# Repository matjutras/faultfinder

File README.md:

# FaultFinder

See `CLAUDE.md` for architecture and conventions.

## Backend

```
cd backend
python3 -m venv .venv && .venv/bin/pip install -r requirements.txt
.venv/bin/uvicorn app.main:app --reload
.venv/bin/pytest -v
```

Requires `ngspice` on PATH (`sudo apt-get install ngspice`) and `kicad` for
`kicad-cli` (`sudo apt-get install kicad`).

`map.json` and `faults.json` under each `devices/*/` are generated, not
committed (see CLAUDE.md) — after a fresh checkout, regenerate them once per
device:

```
curl -X POST http://localhost:8000/api/devices/voltage_divider_01/import
```

## Frontend

```
cd frontend
npm install
npm run dev
npm test
```

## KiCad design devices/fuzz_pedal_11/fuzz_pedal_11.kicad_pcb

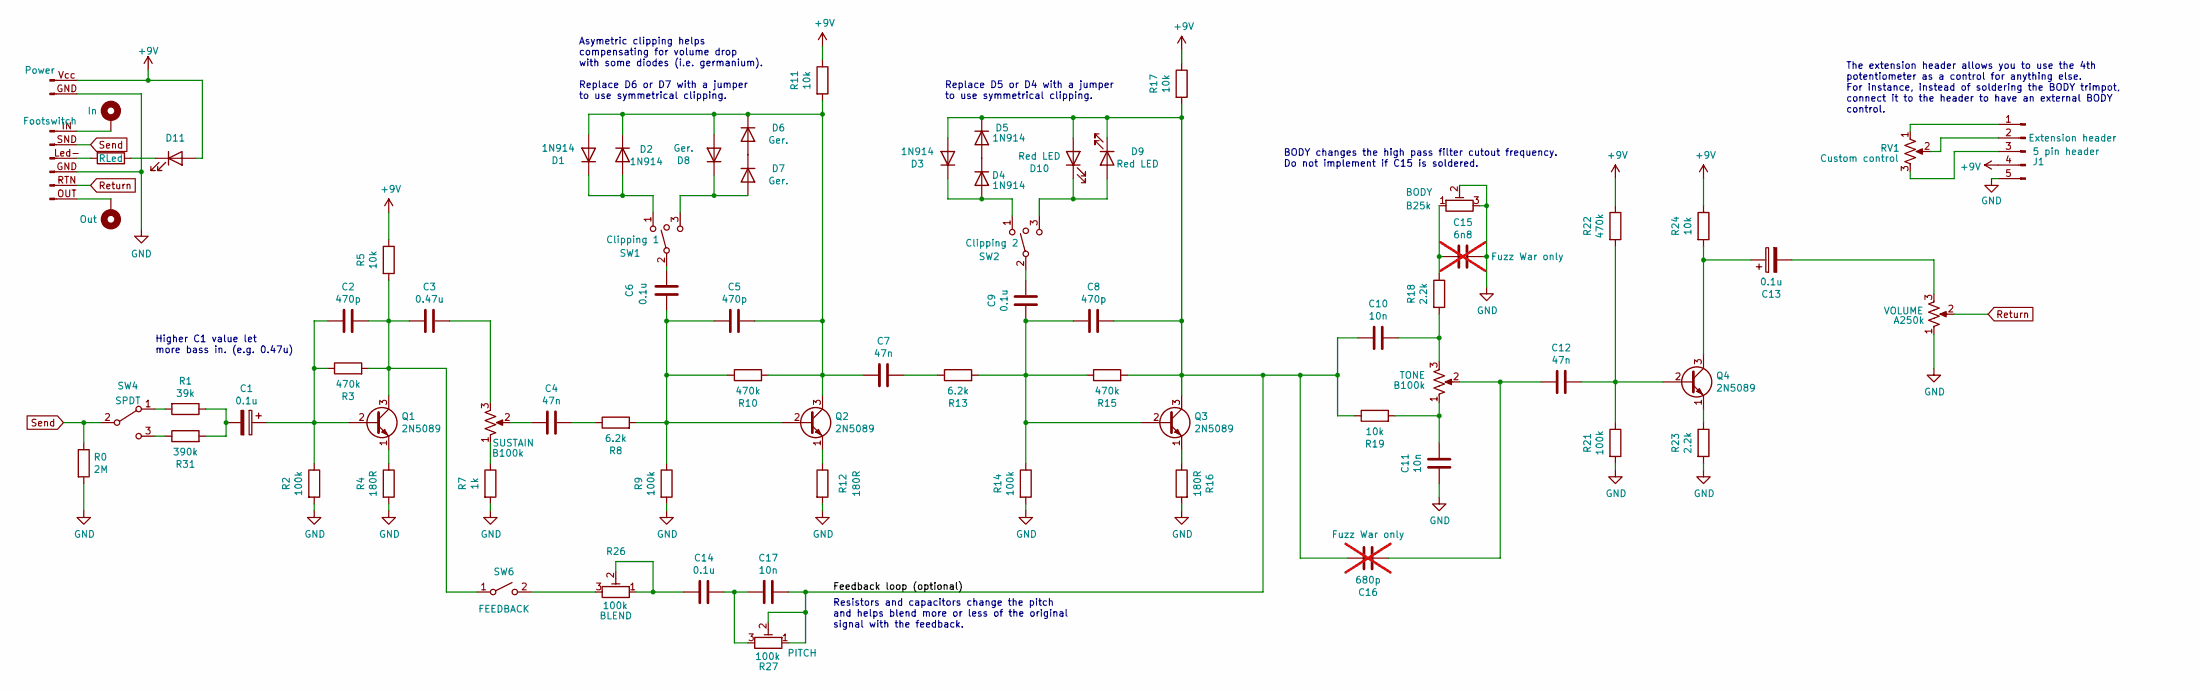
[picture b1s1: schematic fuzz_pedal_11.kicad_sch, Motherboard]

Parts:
C1, C6, C9, C14: 0.1u; C_Rect_L7.2mm_W2.5mm_P5.00mm_FKS2_FKP2_MKS2_MKP2
C2, C5, C8: 470p; C_Rect_L7.2mm_W4.5mm_P5.00mm_FKS2_FKP2_MKS2_MKP2
C3: 0.47u; C_Rect_L7.2mm_W2.5mm_P5.00mm_FKS2_FKP2_MKS2_MKP2
C4, C7, C12: 47n; C_Rect_L7.2mm_W2.5mm_P5.00mm_FKS2_FKP2_MKS2_MKP2
C10, C11, C17: 10n; C_Rect_L7.2mm_W2.5mm_P5.00mm_FKS2_FKP2_MKS2_MKP2
C13: 0.1u; C_Rect_L7.2mm_W3.0mm_P5.00mm_FKS2_FKP2_MKS2_MKP2
C15: 6n8; C_Rect_L7.2mm_W2.5mm_P5.00mm_FKS2_FKP2_MKS2_MKP2; not fitted
C16: 680p; C_Rect_L7.2mm_W2.5mm_P5.00mm_FKS2_FKP2_MKS2_MKP2; not fitted
D1, D2, D3, D4, D5: 1N914; D_DO-35_SOD27_P7.62mm_Horizontal
D6, D7, D8: Ger.; D_DO-35_SOD27_P7.62mm_Horizontal
D9, D10: Red LED; LED_D5.0mm
D11: LED 5mm; LED_D5.0mm
DC-Header1: JST connector 2 pin; Connector_Header_DC
H1: In; SolderWire-0.5sqmm_1x01_D0.9mm_OD2.1mm
H2: Out; SolderWire-0.5sqmm_1x01_D0.9mm_OD2.1mm
J1: 5 pin header; PinSocket_1x05_P2.54mm_Vertical
Q1, Q2, Q3, Q4: 2N5089; TO-92_Inline_Wide
R0: 2M; R_Axial_DIN0207_L6.3mm_D2.5mm_P7.62mm_Horizontal
R1: 39k; R_Axial_DIN0207_L6.3mm_D2.5mm_P7.62mm_Horizontal
R2, R9, R14, R21: 100k; R_Axial_DIN0207_L6.3mm_D2.5mm_P7.62mm_Horizontal
R3, R10, R15, R22: 470k; R_Axial_DIN0207_L6.3mm_D2.5mm_P7.62mm_Horizontal
R4, R12, R16: 180R; R_Axial_DIN0207_L6.3mm_D2.5mm_P7.62mm_Horizontal
R5, R11, R17, R19, R24: 10k; R_Axial_DIN0207_L6.3mm_D2.5mm_P7.62mm_Horizontal
R6, R20: B100k; Potentiometer_Alpha_16mm_angled
R7: 1k; R_Axial_DIN0207_L6.3mm_D2.5mm_P7.62mm_Horizontal
R8, R13: 6.2k; R_Axial_DIN0207_L6.3mm_D2.5mm_P7.62mm_Horizontal
R18, R23: 2.2k; R_Axial_DIN0207_L6.3mm_D2.5mm_P7.62mm_Horizontal
R25: A250k; Potentiometer_Alpha_16mm_angled
R26, R27: 100k; Potentiometer_Vishay_T73YP_Vertical
R29: 4k; R_Axial_DIN0207_L6.3mm_D2.5mm_P7.62mm_Horizontal
R30: B25k; Potentiometer_Vishay_T73YP_Vertical
R31: 390k; R_Axial_DIN0207_L6.3mm_D2.5mm_P7.62mm_Horizontal
RV1: ?; Potentiometer_Alpha_16mm_angled
SW1, SW2: SPDT on-off-on; SW_SPDT_Lugs
SW4: SPDT; SW_SPDT_Lugs
SW6: 2.54 pin header to Footswitch; SolderWire-0.5sqmm_1x02_P2.54mm_D0.9mm_OD2.1mm
Switch-Header1: JST connector 2 pin; Connector_Header_Switch

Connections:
+9V: D11.2 (A), DC-Header1.Vcc (Pin_1), J1.4, R5.1, R11.1, R17.1, R22.1, R24.1
/Feedback loop: C8.1, C10.2, C16.1, C17.1, D3.2 (A), D5.1 (K), D9.1 (K), D10.2 (A), Q3.3 (C), R15.2, R17.2, R19.1, R27.1, R27.2
GND: C11.2, C15.1, DC-Header1.GND (Pin_2), J1.5, R0.2, R2.2, R4.2, R7.2, R9.2, R12.2, R14.2, R16.2, R21.2, R23.2, R25.1, R30.2, R30.3, Switch-Header1.GND (Pin_5)
unnamed: C1.2, R1.1, R31.2
unnamed: C3.1, R6.3
unnamed: C4.1, R8.1
unnamed: C4.2, R6.2
unnamed: C6.2, SW1.2
unnamed: C7.1, R13.1
unnamed: C9.1, SW2.2
unnamed: C10.1, R18.2, R20.3
unnamed: C11.1, R19.2, R20.1
unnamed: C12.2, C16.2, R20.2
unnamed: C13.2, R25.3
unnamed: C14.1, C17.2, R27.3
unnamed: C14.2, R26.1, R26.2
unnamed: C15.2, R18.1, R30.1
unnamed: C5.1, C7.2, D1.2 (A), D2.1 (K), D6.1 (K), D8.2 (A), Q2.3 (C), R10.2, R11.2
unnamed: D1.1 (K), D2.2 (A), SW1.1
unnamed: D3.1 (K), D4.2 (A), SW2.1
unnamed: D4.1 (K), D5.2 (A)
unnamed: D6.2 (A), D7.1 (K)
unnamed: D7.2 (A), D8.1 (K), SW1.3
unnamed: D9.2 (A), D10.1 (K), SW2.3
unnamed: D11.1 (K), R29.1
unnamed: J1.1, RV1.1
unnamed: J1.2, RV1.2
unnamed: J1.3, RV1.3
unnamed: C1.1, C2.2, Q1.2 (B), R2.1, R3.1
unnamed: C2.1, C3.2, Q1.3 (C), R3.2, R5.2, SW6.1 (A)
unnamed: Q1.1 (E), R4.1
unnamed: C5.2, C6.1, Q2.2 (B), R8.2, R9.1, R10.1
unnamed: Q2.1 (E), R12.1
unnamed: C8.2, C9.2, Q3.2 (B), R13.2, R14.1, R15.1
unnamed: Q3.1 (E), R16.1
unnamed: C12.1, Q4.2 (B), R21.1, R22.2
unnamed: C13.1, Q4.3 (C), R24.2
unnamed: Q4.1 (E), R23.1
unnamed: R6.1, R7.1
unnamed: R1.2, SW4.1 (A)
unnamed: R31.1, SW4.3 (C)
unnamed: R26.3, SW6.2 (B)
unnamed: H1.1, Switch-Header1.IN (Pin_1)
unnamed: R29.2, Switch-Header1.Led- (Pin_4)
unnamed: H2.1, Switch-Header1.OUT (Pin_7)
Return: R25.2, Switch-Header1.RTN (Pin_6)
Send: R0.1, SW4.2 (B), Switch-Header1.SND (Pin_2)

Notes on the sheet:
BODY changes the high pass filter cutout frequency. Do not implement if C15 is soldered.
Resistors and capacitors change the pitch and helps blend more or less of the original signal with the feedback.
Higher C1 value let more bass in. (e.g. 0.47u)
The extension header allows you to use the 4th potentiometer as a control for anything else. For instance, instead of soldering the BODY trimpot, connect it to the header to have an external BODY control.
Replace D5 or D4 with a jumper to use symmetrical clipping.
Asymetric clipping helps compensating for volume drop with some diodes (i.e. germanium). Replace D6 or D7 with a jumper to use symmetrical clipping.

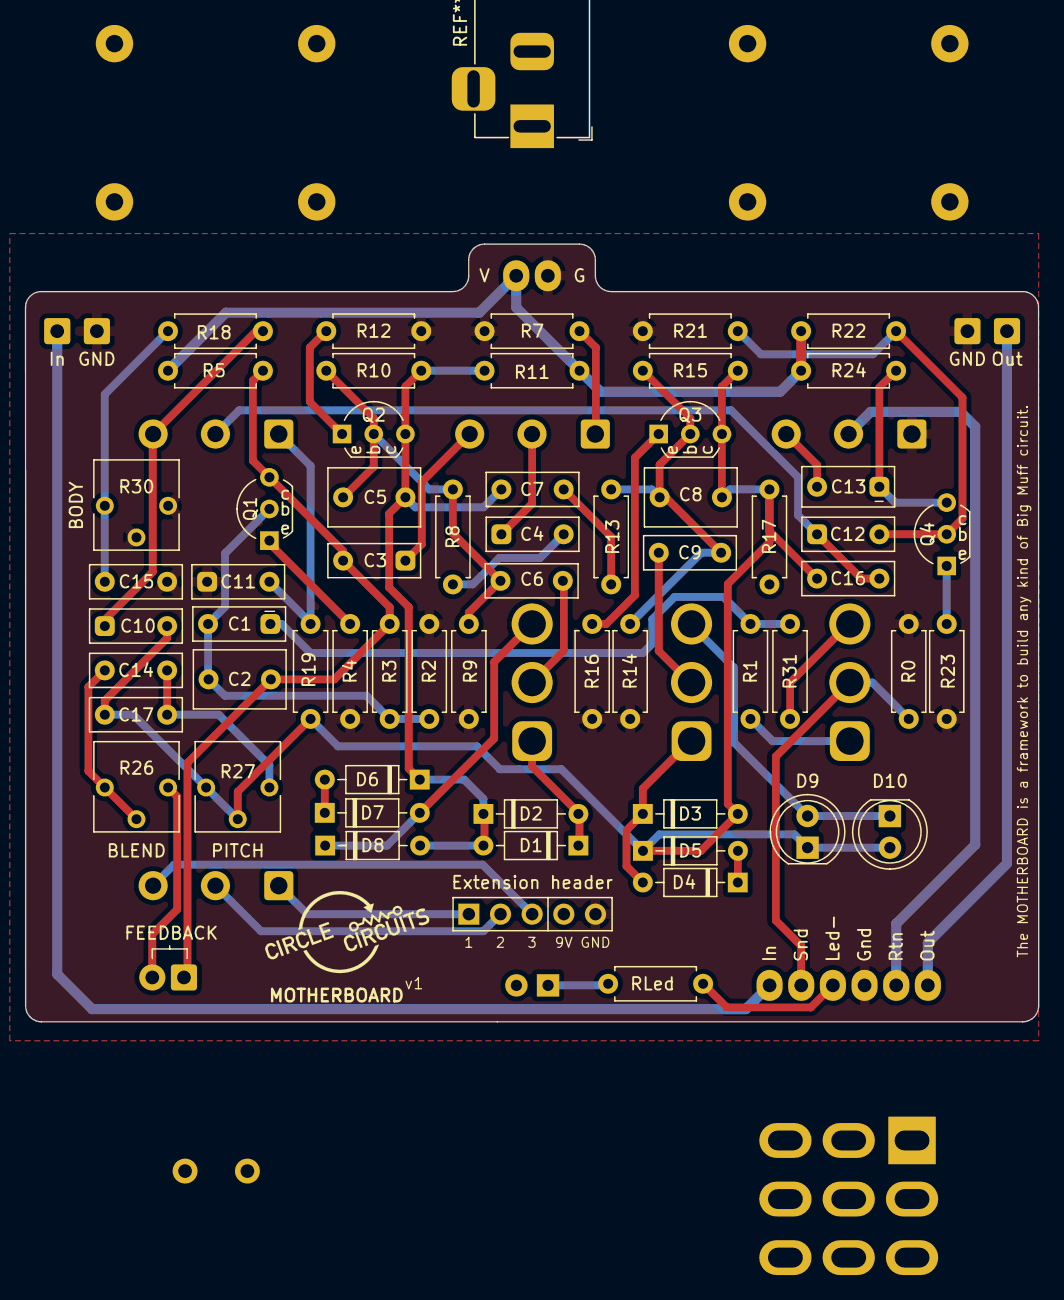
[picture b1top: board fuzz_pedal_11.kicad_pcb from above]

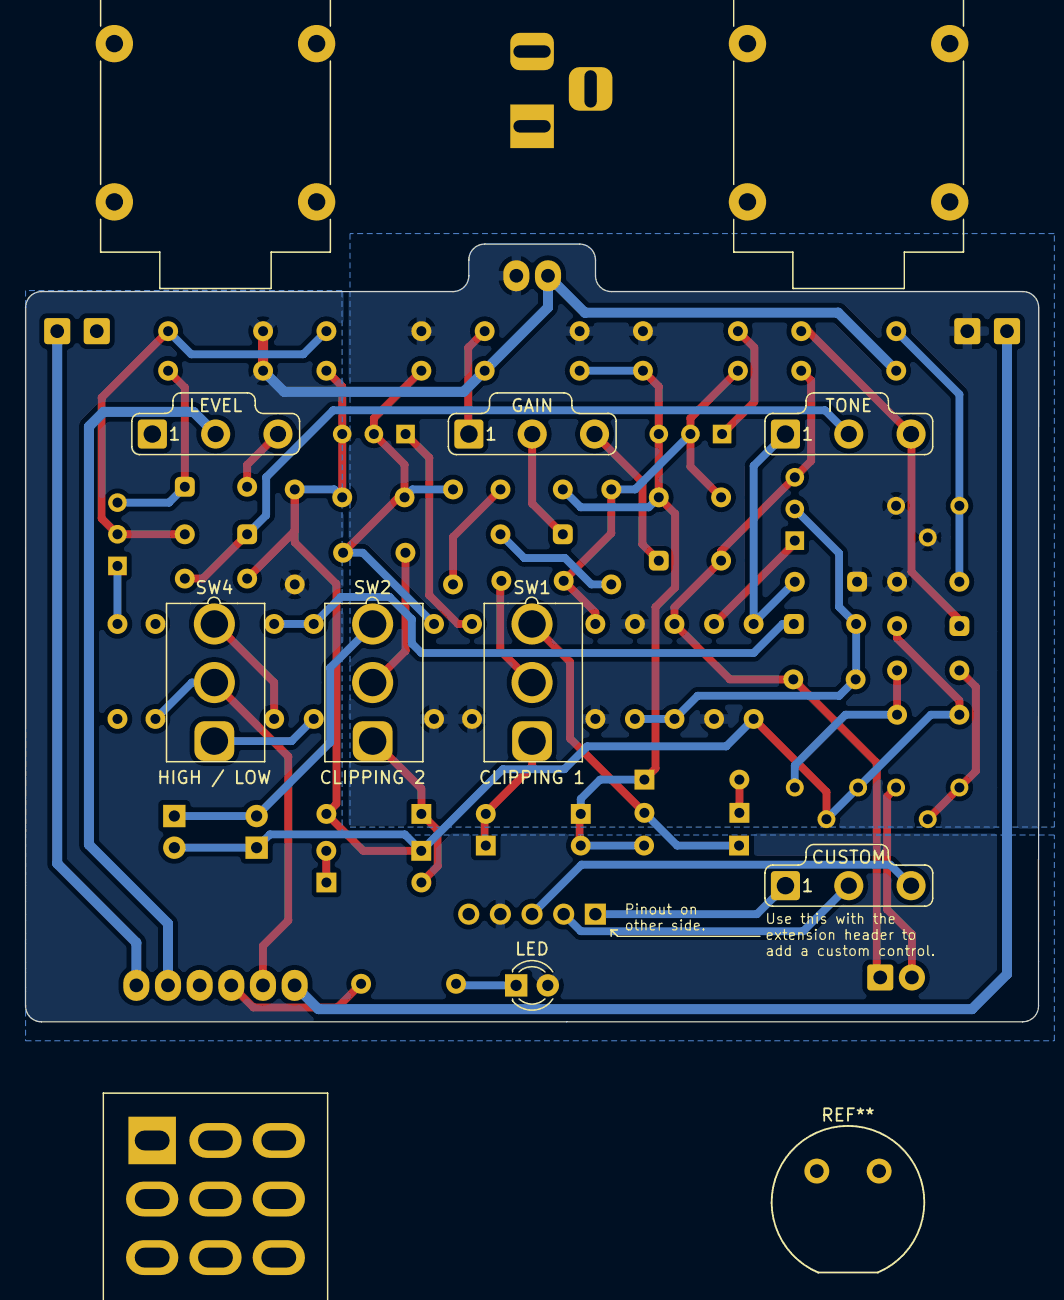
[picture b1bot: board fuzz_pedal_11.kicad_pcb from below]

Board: 2 copper layers, 81.3 x 62.4 mm, 74 parts (9 on the bottom side), 47 nets.

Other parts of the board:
Ref: Val; Switch_Alpha_SF17010F-0302-21R-L.step

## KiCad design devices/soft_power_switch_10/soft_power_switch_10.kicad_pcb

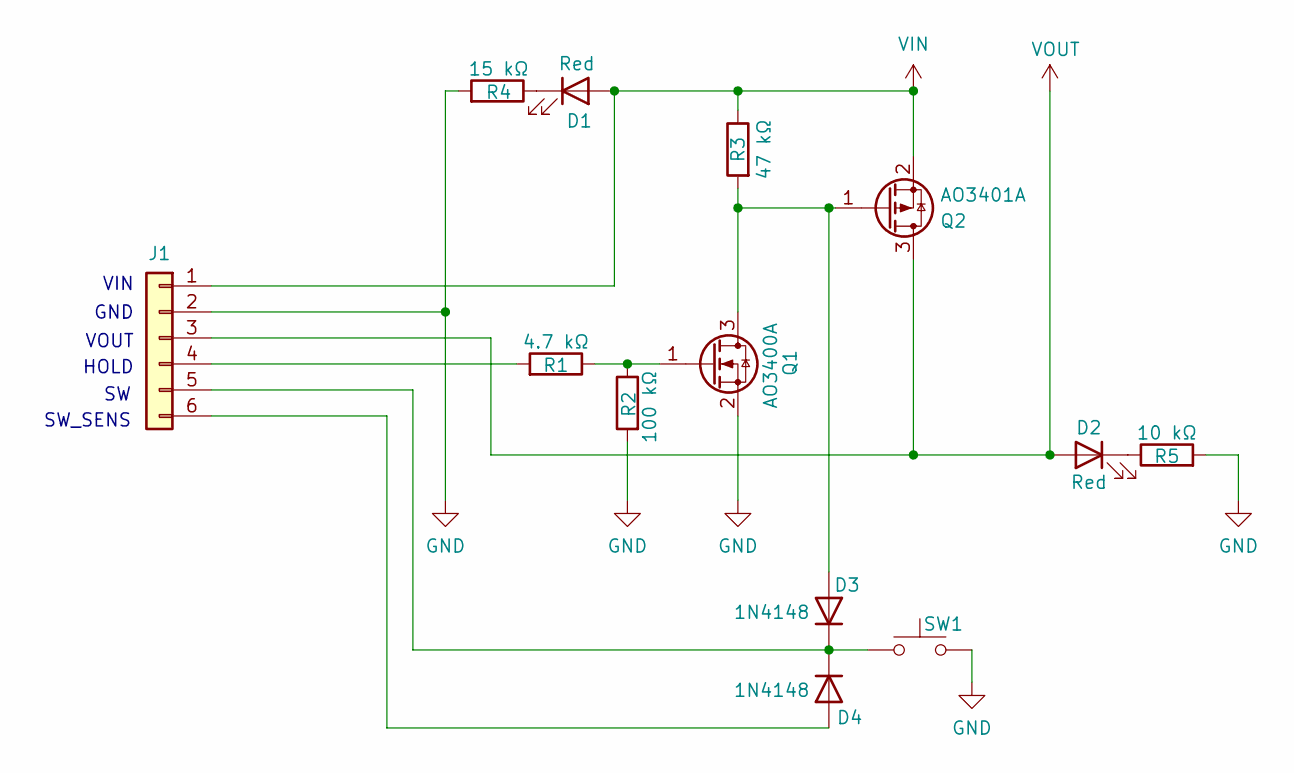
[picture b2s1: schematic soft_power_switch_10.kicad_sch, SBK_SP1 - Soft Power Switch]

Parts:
D1, D2: Red; LED_0603_1608Metric
D3, D4: 1N4148; D_SOD-323; LCSC C2128
J1: Conn_01x06; PinHeader_1x06_P2.54mm_Vertical
Q1: AO3400A; SOT-23
Q2: AO3401A; SOT-23
R1: 4.7 kΩ; R_0402_1005Metric
R2: 100 kΩ; R_0603_1608Metric
R3: 47 kΩ; R_0402_1005Metric
R4: 15 kΩ; R_0402_1005Metric
R5: 10 kΩ; R_0402_1005Metric
SW1: TS-1088-AR02016; SW_SPST_TS-1088-xR020; LCSC C720477

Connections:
GND: J1.2, Q1.2 (S), R2.2, R4.2, R5.2, SW1.2
unnamed: D1.1 (K), R4.1
unnamed: D2.1 (K), R5.1
unnamed: D3.2 (A), Q1.3 (D), Q2.1 (G), R3.2
unnamed: D3.1 (K), D4.1 (K), J1.5, SW1.1
unnamed: D4.2 (A), J1.6
unnamed: J1.4, R1.2
unnamed: Q1.1 (G), R1.1, R2.1
VIN: D1.2 (A), J1.1, Q2.2 (S), R3.1
VOUT: D2.2 (A), J1.3, Q2.3 (D)

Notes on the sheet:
VOUT
VIN
HOLD
SW_SENS
GND

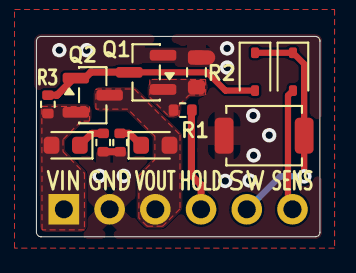
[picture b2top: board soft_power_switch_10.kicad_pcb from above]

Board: 2 copper layers, 15.7 x 11.1 mm, 13 parts (1 on the bottom side), 10 nets.

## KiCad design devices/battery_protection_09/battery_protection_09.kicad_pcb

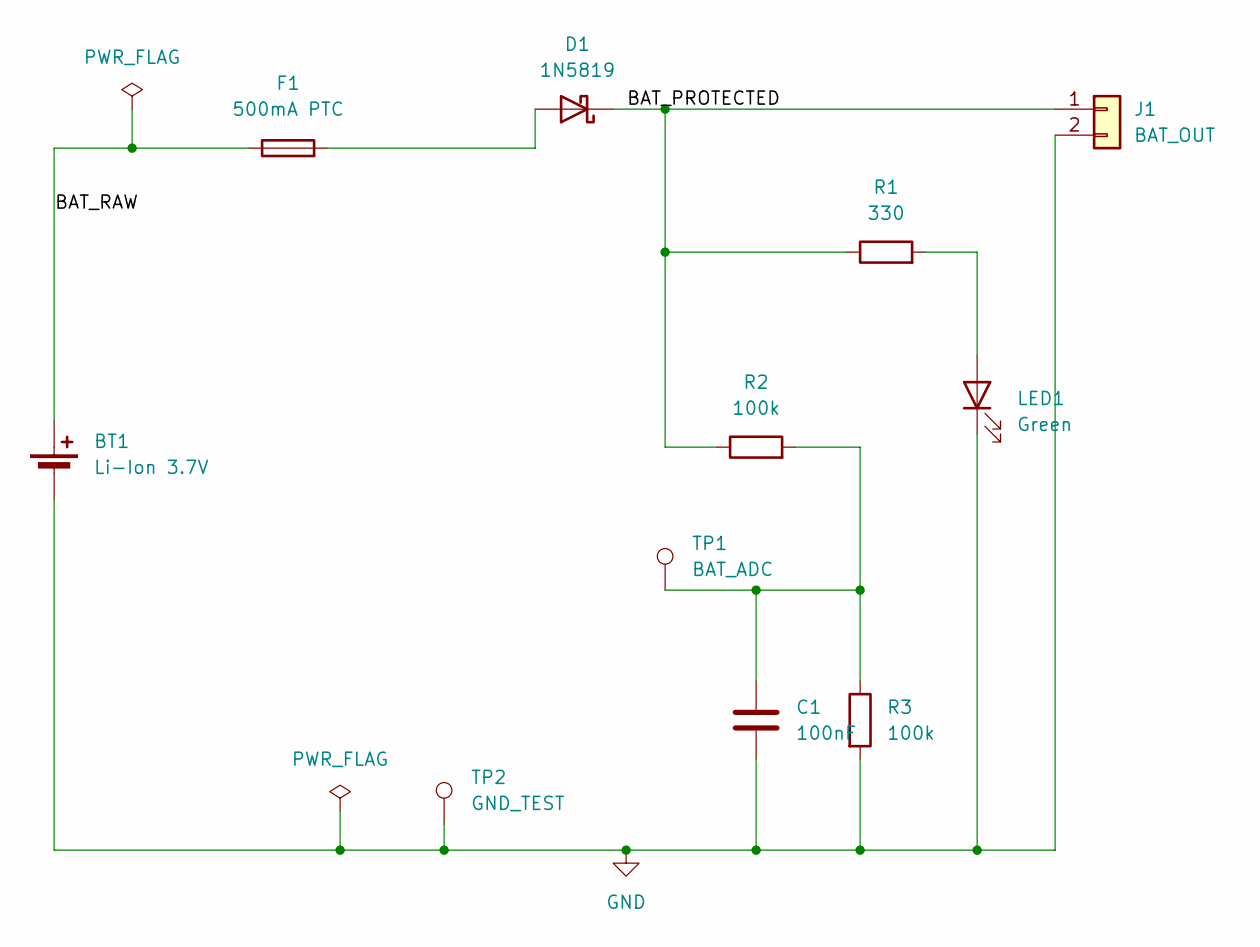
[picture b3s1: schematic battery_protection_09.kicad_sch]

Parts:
BT1: Li-Ion 3.7V; BatteryHolder_Keystone_1042_1x18650
C1: 100nF; C_0805_2012Metric
D1: 1N5819; D_SMA
F1: 500mA PTC; Fuse_1206_3216Metric
J1: BAT_OUT; PinHeader_1x02_P2.54mm_Vertical
LED1: Green; LED_0805_2012Metric
R1: 330; R_0805_2012Metric
R2, R3: 100k; R_0805_2012Metric
TP1: BAT_ADC; TestPoint_Pad_D1.5mm
TP2: GND_TEST; TestPoint_Pad_D1.5mm

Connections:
/BAT_PROTECTED: D1.1 (K), J1.1, R1.1, R2.1
/BAT_RAW: BT1.1 (+), F1.1
GND: BT1.2 (-), C1.2, J1.2, LED1.1 (K), R3.2, TP2.1 (1_1)
unnamed: C1.1, R2.2, R3.1, TP1.1 (1_1)
unnamed: D1.2 (A), F1.2
unnamed: LED1.2 (A), R1.2

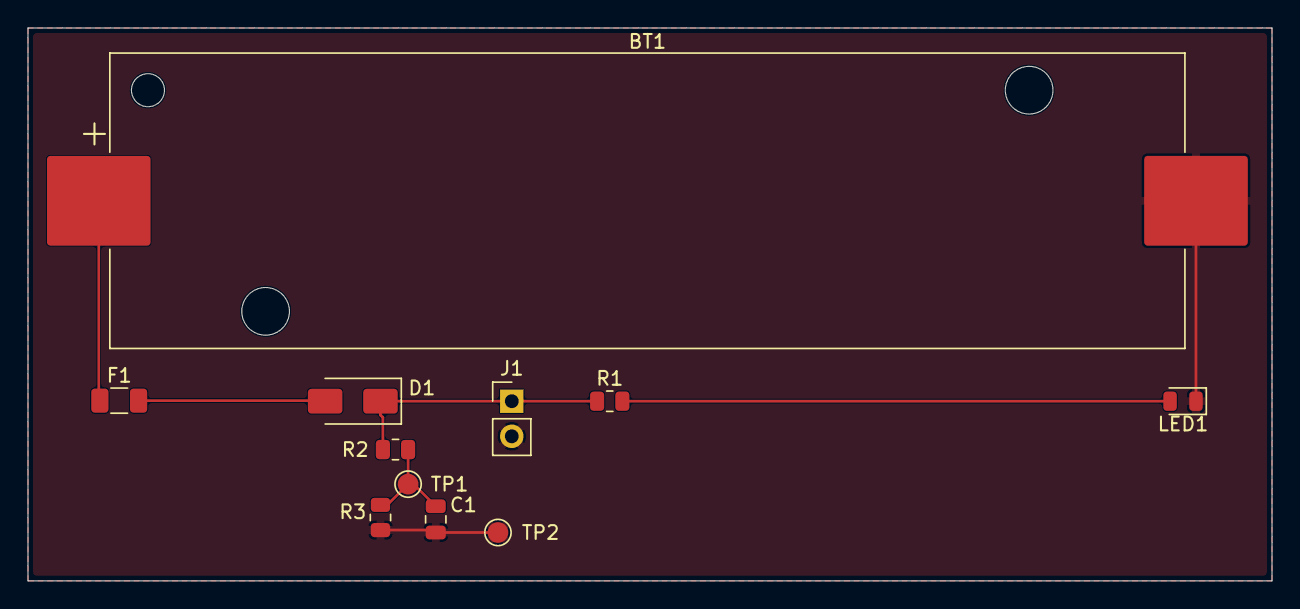
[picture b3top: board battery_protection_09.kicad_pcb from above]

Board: 2 copper layers, 90.0 x 40.0 mm, 11 parts (0 on the bottom side), 6 nets.

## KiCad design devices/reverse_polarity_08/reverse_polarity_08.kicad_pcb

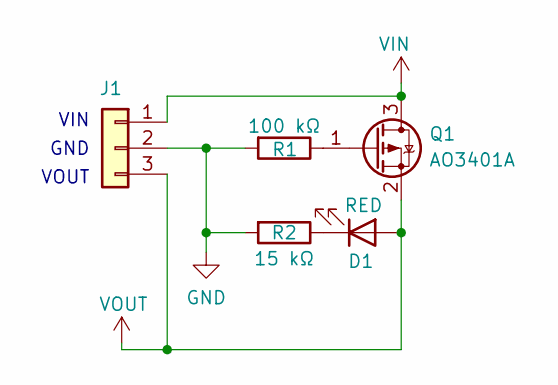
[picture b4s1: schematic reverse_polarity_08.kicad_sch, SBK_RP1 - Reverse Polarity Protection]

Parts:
D1: RED; LED_0603_1608Metric
J1: 1 x 3 pin header; PinHeader_1x03_P2.54mm_Vertical
Q1: AO3401A; SOT-23
R1: 100 kΩ; R_0603_1608Metric
R2: 15 kΩ; R_0402_1005Metric

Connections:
GND: J1.2, R1.2, R2.2
unnamed: D1.1 (K), R2.1
unnamed: Q1.1 (G), R1.1
VIN: J1.1, Q1.3 (D)
VOUT: D1.2 (A), J1.3, Q1.2 (S)

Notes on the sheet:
GND
VOUT
VIN

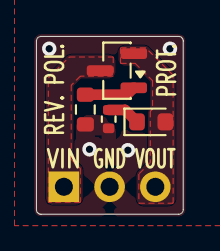
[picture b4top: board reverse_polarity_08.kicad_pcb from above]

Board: 2 copper layers, 8.2 x 9.9 mm, 5 parts (1 on the bottom side), 5 nets.

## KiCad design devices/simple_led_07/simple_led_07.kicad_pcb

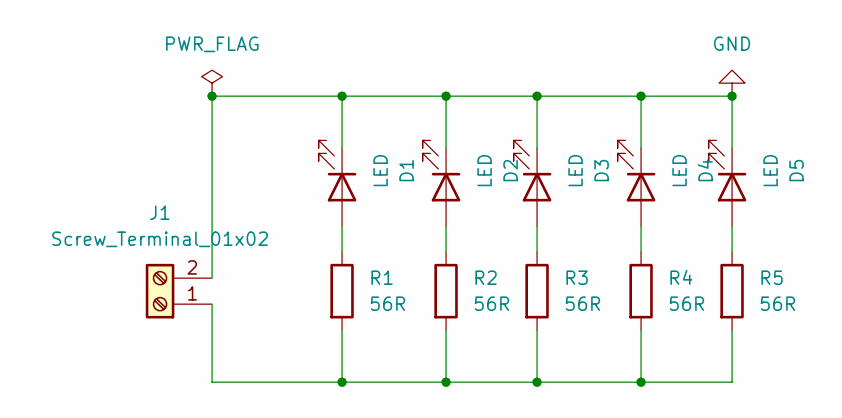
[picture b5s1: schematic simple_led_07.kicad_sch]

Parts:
D1, D2, D3, D4, D5: LED; LED_0805_2012Metric
J1: Screw_Terminal_01x02; TerminalBlock_MaiXu_MX126-5.0-02P_1x02_P5.00mm
R1, R2, R3, R4, R5: 56R; R_0805_2012Metric

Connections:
GND: D1.1 (K), D2.1 (K), D3.1 (K), D4.1 (K), D5.1 (K), J1.2
unnamed: D1.2 (A), R1.1
unnamed: D2.2 (A), R2.1
unnamed: D3.2 (A), R3.1
unnamed: D4.2 (A), R4.1
unnamed: D5.2 (A), R5.1
unnamed: J1.1, R1.2, R2.2, R3.2, R4.2, R5.2

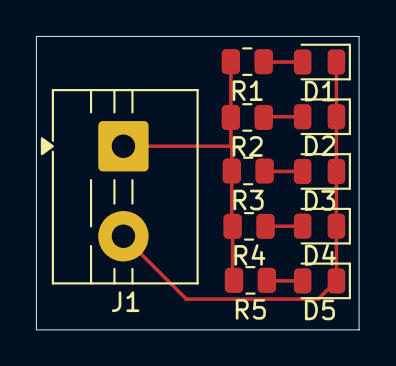
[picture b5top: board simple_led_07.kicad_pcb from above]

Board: 2 copper layers, 17.9 x 16.3 mm, 11 parts (0 on the bottom side), 7 nets.

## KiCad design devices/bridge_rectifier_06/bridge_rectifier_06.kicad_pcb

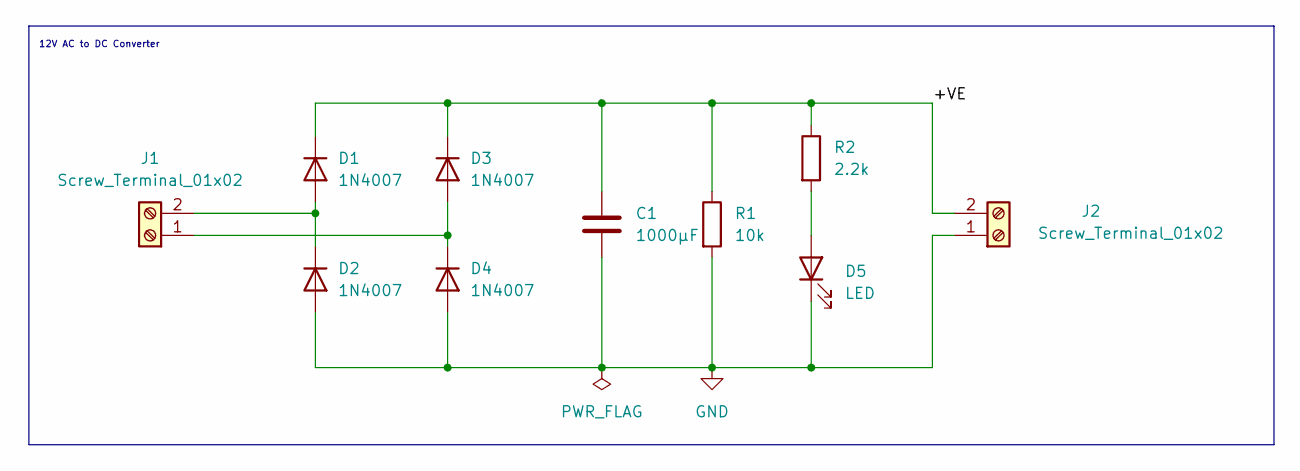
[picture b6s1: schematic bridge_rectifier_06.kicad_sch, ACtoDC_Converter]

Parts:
C1: 1000µF; CP_Radial_D8.0mm_P3.50mm
D1, D2, D3, D4: 1N4007; D_DO-41_SOD81_P10.16mm_Horizontal
D5: LED; LED_D5.0mm
J1, J2: Screw_Terminal_01x02; TerminalBlock_MaiXu_MX126-5.0-02P_1x02_P5.00mm
R1: 10k; R_Axial_DIN0204_L3.6mm_D1.6mm_P7.62mm_Horizontal
R2: 2.2k; R_Axial_DIN0204_L3.6mm_D1.6mm_P7.62mm_Horizontal

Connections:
/+VE: C1.1, D1.1 (K), D3.1 (K), J2.2, R1.1, R2.1
GND: C1.2, D2.2 (A), D4.2 (A), D5.1 (K), J2.1, R1.2
unnamed: D1.2 (A), D2.1 (K), J1.2
unnamed: D3.2 (A), D4.1 (K), J1.1
unnamed: D5.2 (A), R2.2

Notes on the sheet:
12V AC to DC Converter

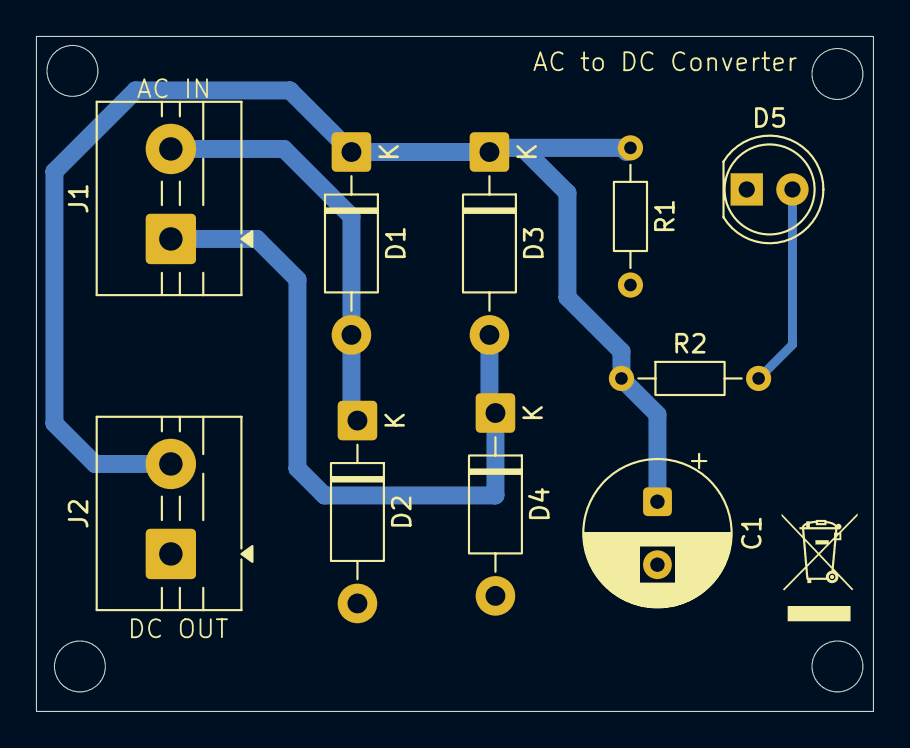
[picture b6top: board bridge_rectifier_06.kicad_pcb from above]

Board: 2 copper layers, 46.5 x 37.5 mm, 10 parts (0 on the bottom side), 5 nets.

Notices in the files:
devices/reverse_polarity_08/reverse_polarity_08.kicad_sch:
Licensed under CERN-OHL-P-2.0
